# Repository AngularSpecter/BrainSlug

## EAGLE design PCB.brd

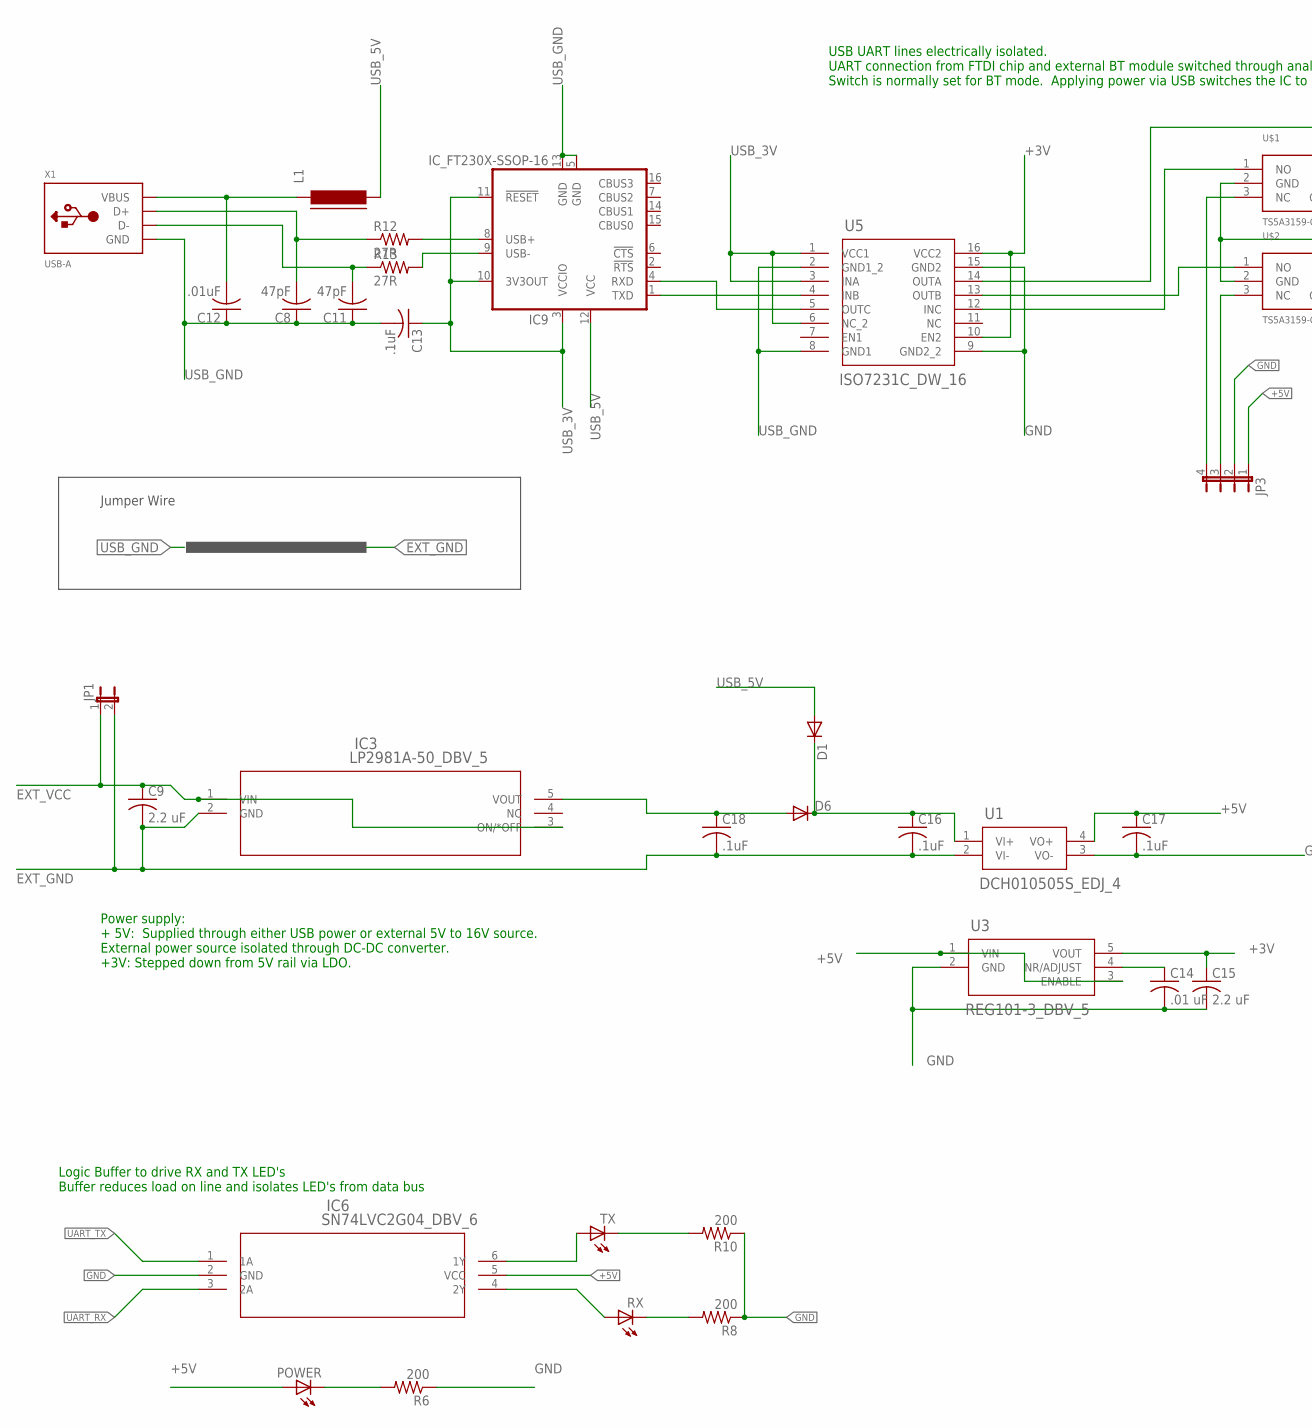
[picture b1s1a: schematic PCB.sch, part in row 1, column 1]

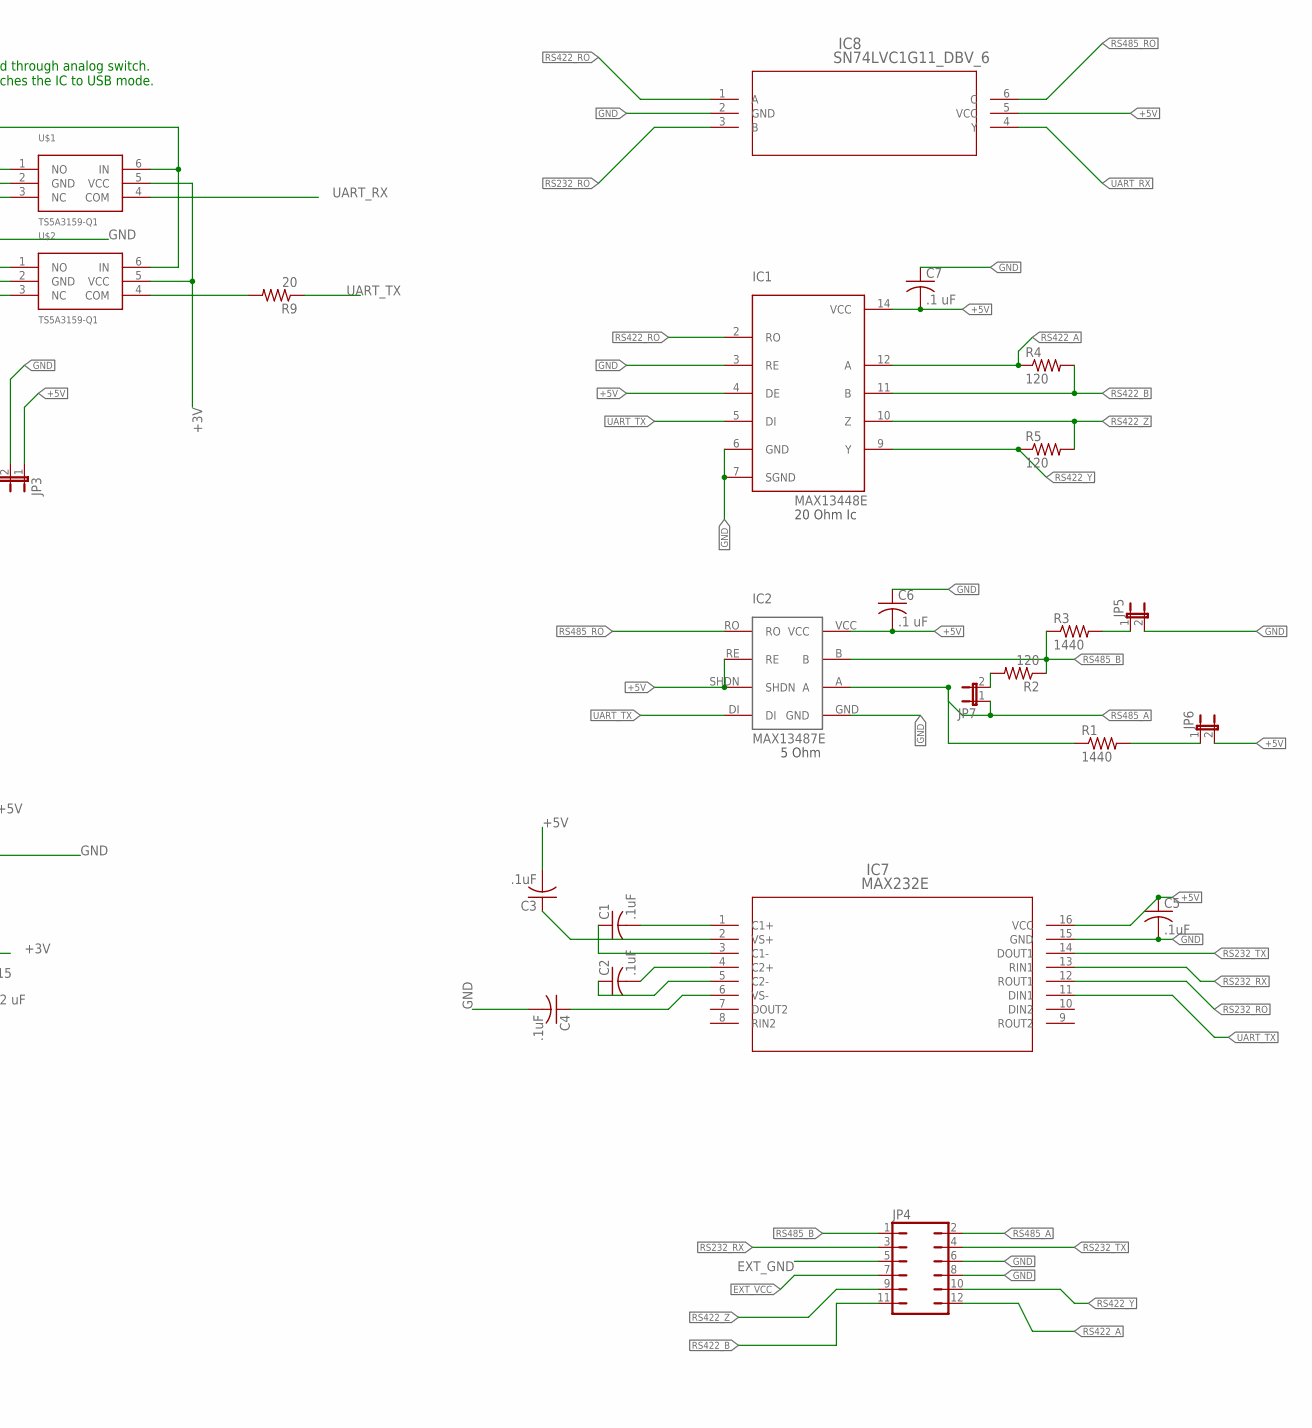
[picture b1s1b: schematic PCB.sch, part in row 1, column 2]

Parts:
C1, C2, C3, C4, C5, C13, C16, C17, C18: .1uF; C1206
C6, C7: .1 uF; C1206
C8, C11: 47pF; C1206
C9, C15: 2.2 uF; C1206
C12: .01uF; C1206
C14: .01 uF; C1206
D1, D6: DIODE-SOT23; SOT-23
IC1: MAX13448E; SO14(N)
IC2: MAX13487E
IC3: LP2981A-50_DBV_5; DBV5
IC6: SN74LVC2G04_DBV_6; DBV6
IC7: MAX232E; D16
IC8: SN74LVC1G11_DBV_6; DBV6
IC9: IC_FT230X-SSOP-16; SSOP-16-FTDI
JP1, JP5, JP6, JP7: JP1E; JP1
JP3: JP4E; JP4
JP4: JP6Q
L1: FERRITE-1206; FB1206
POWER: LEDSMT1206; 1206
R1, R3: 1440; M1206
R2: 120; M1206
R4, R5: 120; R1206
R6, R8, R10: 200; M1206
R9: 20; M1206
R12, R13: 27R; R1206
RX: LEDSMT1206; 1206
TX: LEDSMT1206; 1206
U1: DCH010505S_EDJ_4; EDJ4
U3: REG101-3_DBV_5; DBV5
U5: ISO7231C_DW_16; DW16
U$1, U$2: TS5A3159-Q1; DBV6
X1: USB-A; MOLEX_480371000

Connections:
+3V: C15.1, U3.5 (VOUT), U5.10 (EN2), U5.16 (VCC2), U$1.5 (VCC), U$2.5 (VCC)
+5V: C3.2, C5.1, C6.2, C7.2, C17.1, IC1.4 (DE), IC1.14 (VCC), IC2.RE, IC2.SHDN, IC2.VCC, IC6.5 (VCC), IC7.16 (VCC), IC8.5 (VCC), JP3.1, JP6.2, POWER.A, U1.4 (VO+), U3.1 (VIN), U3.3 (ENABLE)
BT_RX: JP3.4, U$1.3 (NC)
BT_TX: JP3.3, U$2.3 (NC)
EXT_5V: C18.1, D6.1 (A), IC3.5 (VOUT)
EXT_GND: C9.2, C16.2, C18.2, IC3.2 (GND), JP1.2, JP4.5, U1.2 (VI-)
EXT_VCC: C9.1, IC3.1 (VIN), IC3.3 (ON/*OFF), JP1.1, JP4.7
GND: C4.2, C5.2, C6.1, C7.1, C14.2, C15.2, C17.2, IC1.3 (RE), IC1.6 (GND), IC1.7 (SGND), IC2.GND, IC6.2 (GND), IC7.15 (GND), IC8.2 (GND), JP3.2, JP4.6, JP4.8, JP5.2, R6.1, R8.1, R10.1, U1.3 (VO-), U3.2 (GND), U5.9 (GND2_2), U5.15 (GND2), U$1.2 (GND), U$2.2 (GND)
unnamed: IC9.1 (TXD), U5.4 (INB)
unnamed: IC9.4 (RXD), U5.5 (OUTC)
unnamed: POWER.C, R6.2
unnamed: IC9.9 (USB-), R13.2
unnamed: IC9.8 (USB+), R12.2
unnamed: C8.2, R12.1, X1.3 (D+)
unnamed: C11.2, R13.1, X1.2 (D-)
unnamed: C14.1, U3.4 (NR/ADJUST)
RS232_C1+: C1.2, IC7.1 (C1+)
RS232_C1-: C1.1, IC7.3 (C1-)
RS232_C2+: C2.2, IC7.4 (C2+)
RS232_C2-: C2.1, IC7.5 (C2-)
RS232_RO: IC7.12 (ROUT1), IC8.3 (B)
RS232_RX: IC7.13 (RIN1), JP4.3
RS232_TX: IC7.14 (DOUT1), JP4.4
RS232_VS+: C3.1, IC7.2 (VS+)
RS232_VS-: C4.1, IC7.6 (VS-)
RS422_A: IC1.12 (A), JP4.12, R4.1
RS422_B: IC1.11 (B), JP4.11, R4.2
RS422_RO: IC1.2 (RO), IC8.1 (A)
RS422_Y: IC1.9 (Y), JP4.10, R5.1
RS422_Z: IC1.10 (Z), JP4.9, R5.2
RS485TERM: JP7.2, R2.2
RS485_A: IC2.A, JP4.2, JP7.1, R1.1
RS485_B: IC2.B, JP4.1, R2.1, R3.1
RS485_BIASDOWN: JP5.1, R3.2
RS485_BIASUP: JP6.1, R1.2
RS485_RO: IC2.RO, IC8.6 (C)
RX_LED: IC6.4 (2Y), RX.A
RX_LED2: R8.2, RX.C
TX_LED: IC6.6 (1Y), TX.A
TX_LED2: R10.2, TX.C
UART_RX: IC6.3 (2A), IC8.4 (Y), U$1.4 (COM)
UART_TX: IC1.5 (DI), IC2.DI, IC6.1 (1A), IC7.11 (DIN1), R9.1
UART_TX_1: R9.2, U$2.4 (COM)
USB_3V: C13.1, IC9.3 (VCCIO), IC9.10 (3V3OUT), IC9.11 (!RESET), U5.1 (VCC1), U5.3 (INA), U5.6 (NC_2)
USB_5V: D1.1 (A), IC9.12 (VCC), L1.2
USB_GND: C8.1, C11.1, C12.1, C13.2, IC9.5 (GND), IC9.13 (GND), U5.2 (GND1_2), U5.8 (GND1), X1.4 (GND)
USB_RX: U5.12 (INC), U$1.1 (NO)
USB_SWITCH: U5.14 (OUTA), U$1.6 (IN), U$2.6 (IN)
USB_TX: U5.13 (OUTB), U$2.1 (NO)
USB_VCC: C16.1, D1.3 (C), D6.3 (C), U1.1 (VI+)
VCC_USB: C12.2, L1.1, X1.1 (VBUS)

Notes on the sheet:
20 Ohm Ic
5 Ohm
Power supply: + 5V: Supplied through either USB power or external 5V to 16V source. External power source isolated through DC-DC converter. +3V: Stepped down from 5V rail via LDO.
USB UART lines electrically isolated. UART connection from FTDI chip and external BT module switched through analog switch. Switch is normally set for BT mode. Applying power via USB switches the IC to USB mode.
Logic Buffer to drive RX and TX LED's Buffer reduces load on line and isolates LED's from data bus
Jumper Wire

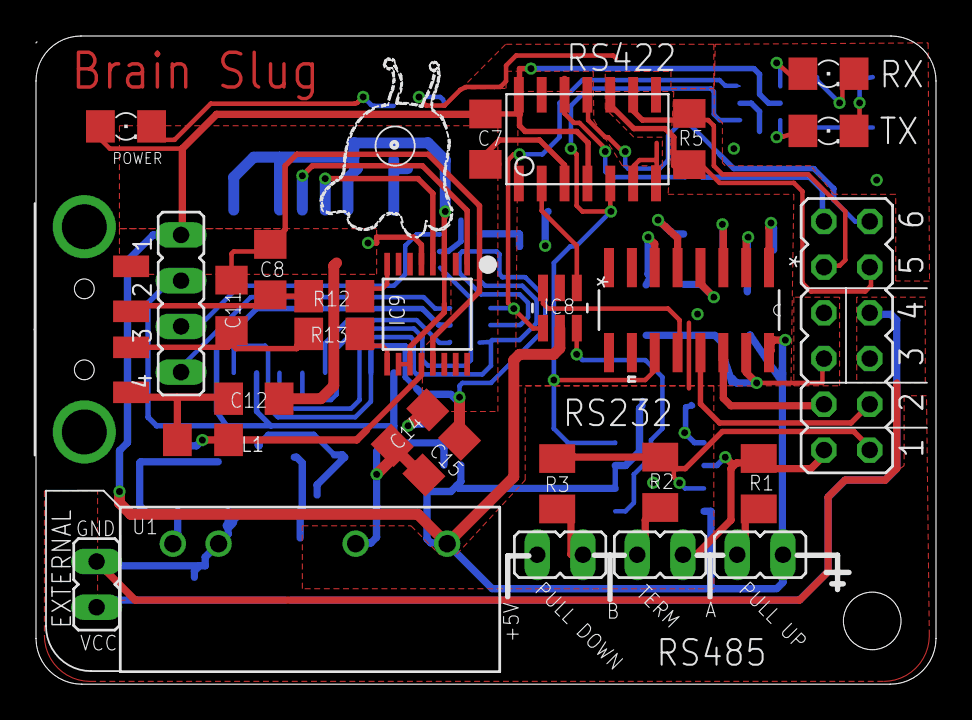
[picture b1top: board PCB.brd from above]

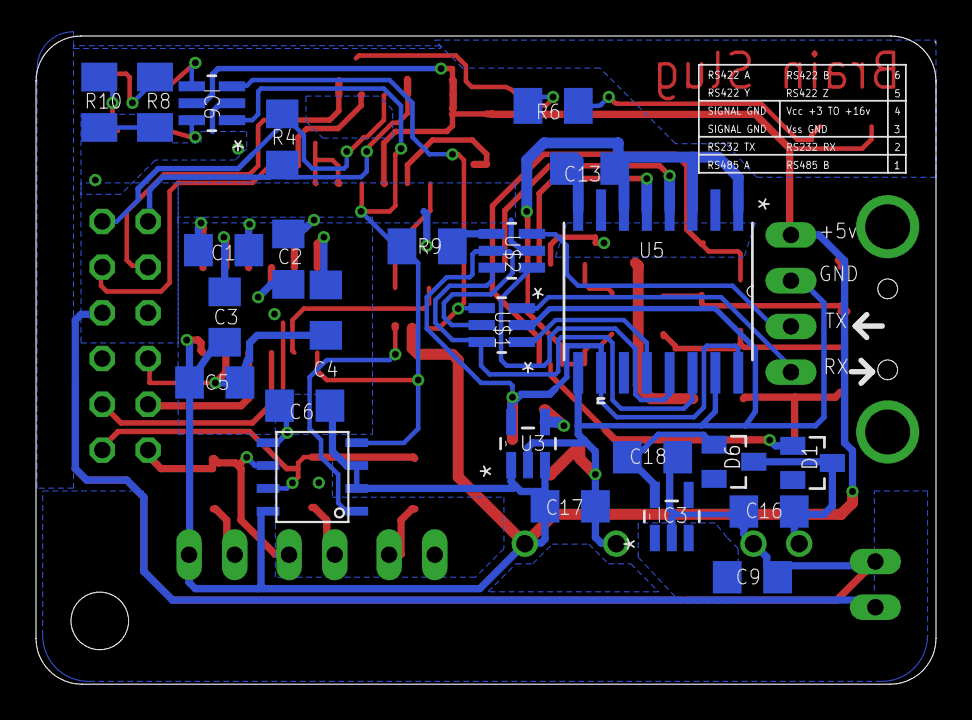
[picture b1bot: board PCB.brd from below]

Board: 2 copper layers, 50.0 x 36.0 mm, 53 parts (25 on the bottom side), 51 nets.

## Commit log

2013-01-18 Initial commit of Eagle PCB files
2013-01-18 Added license
2013-01-30 Layout and silk screen tweaks
2013-04-01 REV 1.2
    Added onboard USB and supply isolation
2013-05-01 Create Eratta
2013-05-01 updates to document V1rA Eratta
2013-05-02 Update Eratta
